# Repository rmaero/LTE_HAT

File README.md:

4G HAT para Raspberry Pi, Diseño completo de un HAT compatible con Raspberry Pi que integra comunicaciones celulares 4G/LTE. Hecho especialmente para usar como companion computer en y comunicarse con un PixHawk en un UAV (unmanned aerial vehicle).
Desarrollado como proyecto final para la materia Diseño Avanzado de Circuitos Impresos en la Universidad Nacional de Rosario.

Dentro del repositorio se van a encontrar 3 versiones del layout apenas diferentes entre si. Estas iteraciones se hicieron en busqueda de optimizar el espacio y la comodidad de los conectores para el usuario (tener en cuenta que una vez estar montado sobre una Raspberry Pi la cara inferior del HAT no es accesible).

Características

Compatible con estándar Raspberry Pi HAT
Cumple especificaciones mecánicas (65x56mm, mounting holes)
EEPROM de identificación según estándar HAT
Conectores GPIO de 40 pines

Comunicacion UART PixHawk:
Conector JST GH 6 pines para conectar con cable cruzado a GPS2 o TELEM2 del PixHawk Cube Orange. 115200 baudios.

Comunicaciones 4G/LTE:

Módulo celular: SIM7600
Bandas soportadas: [especificar]
Interfaz USB para comandos AT
Conectores SMA/U.FL para antenas externas

Diseño RF de Alta Frecuencia

PCB multicapa: 2 capas (esto fue eleccion adrede como ejercicio academico, porque es mas dificil lograr impedancia controlada con esta distancia entre capas).
Control de impedancia de 50Ω en líneas de RF
Control de impedancia de 90Ω en lineas USB 2.0
Stackup optimizado para señales high-speed
Matching de impedancia en conexiones de antena

Alimentación
Pack de baterias 2S a 9S (de 7V a 35V). Regulador switching para alimentar la Raspberry Pi, segundo regulador switching alimenta el modulo SIM7600.

Tecnologías Utilizadas

Diseño PCB: KiCAD 9
Capas: 2 layers (Ground plane en ambas capas)
Comunicación: USB, UART, SPI, GPIO
Impedancia controlada: 50Ω para trazas RF, 90Ω diferencial para USB

Esquematico principal

El esquematico completo puede encontrarse en la carpeta del proyecto.

Estado del Proyecto

-Diseño esquemático completo
-Layout PCB con control de impedancia
-Diseño validado en simulación

Estado actual: Proyecto académico completado (2025). Diseño validado, pendiente fabricación y testing.

Licencia
Proyecto académico - Todos los derechos reservados

Contacto
Rodrigo Maero - r.maero@gmail.com

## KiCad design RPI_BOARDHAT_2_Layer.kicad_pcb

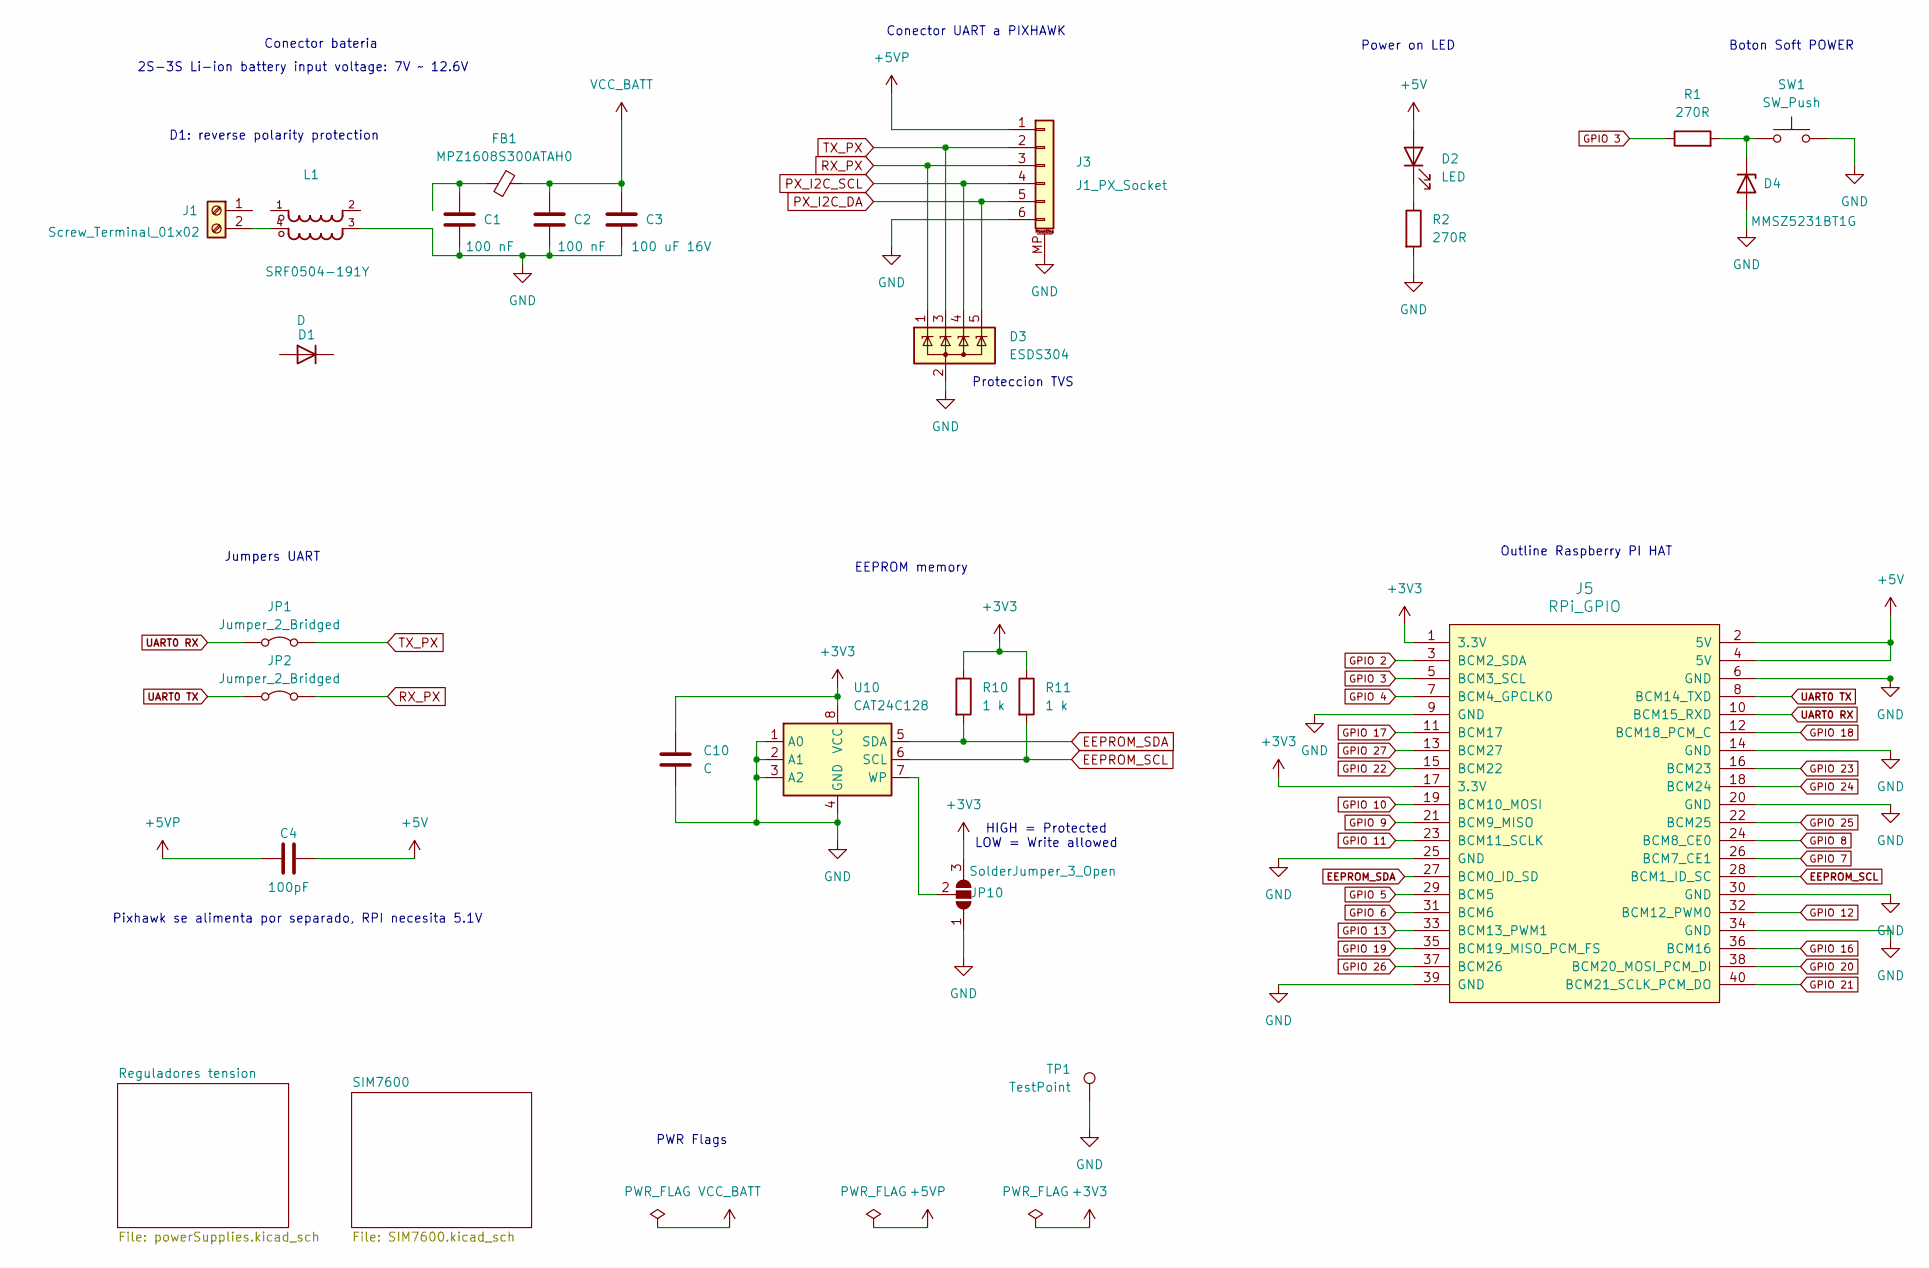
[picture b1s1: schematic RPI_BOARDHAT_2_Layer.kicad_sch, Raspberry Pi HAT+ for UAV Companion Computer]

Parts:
C1, C2: 100 nF; C_0402_1005Metric
C3: 100 uF 16V; C_0402_1005Metric
C4: 100pF; C_0603_1608Metric
C10: C; C_0201_0603Metric
D1: D; D_SMA
D2: LED; LED_0603_1608Metric
D3: ESDS304; SOT-23-5
D4: MMSZ5231BT1G; D_SOD-923
FB1: MPZ1608S300ATAH0; L_0603_1608Metric
J1: Screw_Terminal_01x02; TerminalBlock_bornier-2_P5.08mm
J3: J1_PX_Socket; JST_GH_SM06B-GHS-TB_1x06-1MP_P1.25mm_Horizontal
J5: RPi_GPIO; RPI_Hat_B+
JP1, JP2: Jumper_2_Bridged; SolderJumper-2_P1.3mm_Bridged_RoundedPad1.0x1.5mm
JP10: SolderJumper_3_Open; SolderJumper-3_P1.3mm_Open_Pad1.0x1.5mm_NumberLabels
L1: SRF0504-191Y; FIL_SRF0504-191Y
R1: 270R; R_0201_0603Metric
R2: 270R; R_0603_1608Metric
R10, R11: 1 k; R_0603_1608Metric
SW1: SW_Push; SW_Push_SPST_NO_Alps_SKRK
TP1: TestPoint; TestPoint_2Pads_Pitch2.54mm_Drill0.8mm
U10: CAT24C128; JEITA_SOIC-8_3.9x4.9mm_P1.27mm

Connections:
+3V3: C10.1, J5.1 (3.3V), J5.17 (3.3V), JP10.3 (B), R10.1, R11.1, U10.8 (VCC)
+5V: C4.1, D2.2 (A), J5.2 (5V), J5.4 (5V); also elsewhere on the board
+5VP: C4.2, J3.1
EEPROM_SCL: J5.28 (BCM1_ID_SC), R11.2, U10.6 (SCL)
EEPROM_SDA: J5.27 (BCM0_ID_SD), R10.2, U10.5 (SDA)
GND: C1.2, C2.2, C3.2, C10.2, D3.2 (A), D4.2 (A), J3.6, J3.MP (MountPin), J5.6 (GND), J5.9 (GND), J5.14 (GND), J5.20 (GND), J5.25 (GND), J5.30 (GND), J5.34 (GND), J5.39 (GND), JP10.1 (A), L1.3, R2.2, SW1.2, TP1.1, U10.1 (A0), U10.2 (A1), U10.3 (A2), U10.4 (GND); also elsewhere on the board
GPIO 2: J5.3 (BCM2_SDA)
GPIO 3: J5.5 (BCM3_SCL), R1.1
GPIO 4: J5.7 (BCM4_GPCLK0)
GPIO 5: J5.29 (BCM5)
GPIO 6: J5.31 (BCM6)
GPIO 7: J5.26 (BCM7_CE1)
GPIO 8: J5.24 (BCM8_CE0)
GPIO 9: J5.21 (BCM9_MISO)
GPIO 10: J5.19 (BCM10_MOSI)
GPIO 11: J5.23 (BCM11_SCLK)
GPIO 12: J5.32 (BCM12_PWM0)
GPIO 13: J5.33 (BCM13_PWM1)
GPIO 16: J5.36 (BCM16)
GPIO 17: J5.11 (BCM17)
GPIO 18: J5.12 (BCM18_PCM_C)
GPIO 19: J5.35 (BCM19_MISO_PCM_FS)
GPIO 20: J5.38 (BCM20_MOSI_PCM_DI)
GPIO 21: J5.40 (BCM21_SCLK_PCM_DO)
GPIO 22: J5.15 (BCM22)
GPIO 23: J5.16 (BCM23)
GPIO 24: J5.18 (BCM24)
GPIO 25: J5.22 (BCM25)
GPIO 26: J5.37 (BCM26)
GPIO 27: J5.13 (BCM27)
unnamed: D1.2 (A), L1.2
unnamed: D2.1 (K), R2.1
unnamed: D4.1 (K), R1.2, SW1.1
unnamed: J1.1, L1.1
unnamed: J1.2, L1.4
unnamed: JP10.2 (C), U10.7 (WP)
PX_I2C_DA: D3.5 (K), J3.5
PX_I2C_SCL: D3.4 (K), J3.4
RX_PX: D3.1 (K), J3.3, JP2.2 (B)
TX_PX: D3.3 (K), J3.2, JP1.2 (B)
UART0 RX: J5.10 (BCM15_RXD), JP1.1 (A)
UART0 TX: J5.8 (BCM14_TXD), JP2.1 (A)
VCC_BATT: C2.1, C3.1, FB1.2; also elsewhere on the board

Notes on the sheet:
2S-3S Li-ion battery input voltage: 7V ~ 12.6V
Proteccion TVS
PWR Flags
Pixhawk se alimenta por separado, RPI necesita 5.1V
D1: reverse polarity protection
EEPROM memory
Outline Raspberry PI HAT
Conector UART a PIXHAWK
Jumpers UART
HIGH = Protected LOW = Write allowed
Boton Soft POWER
Conector bateria
Power on LED

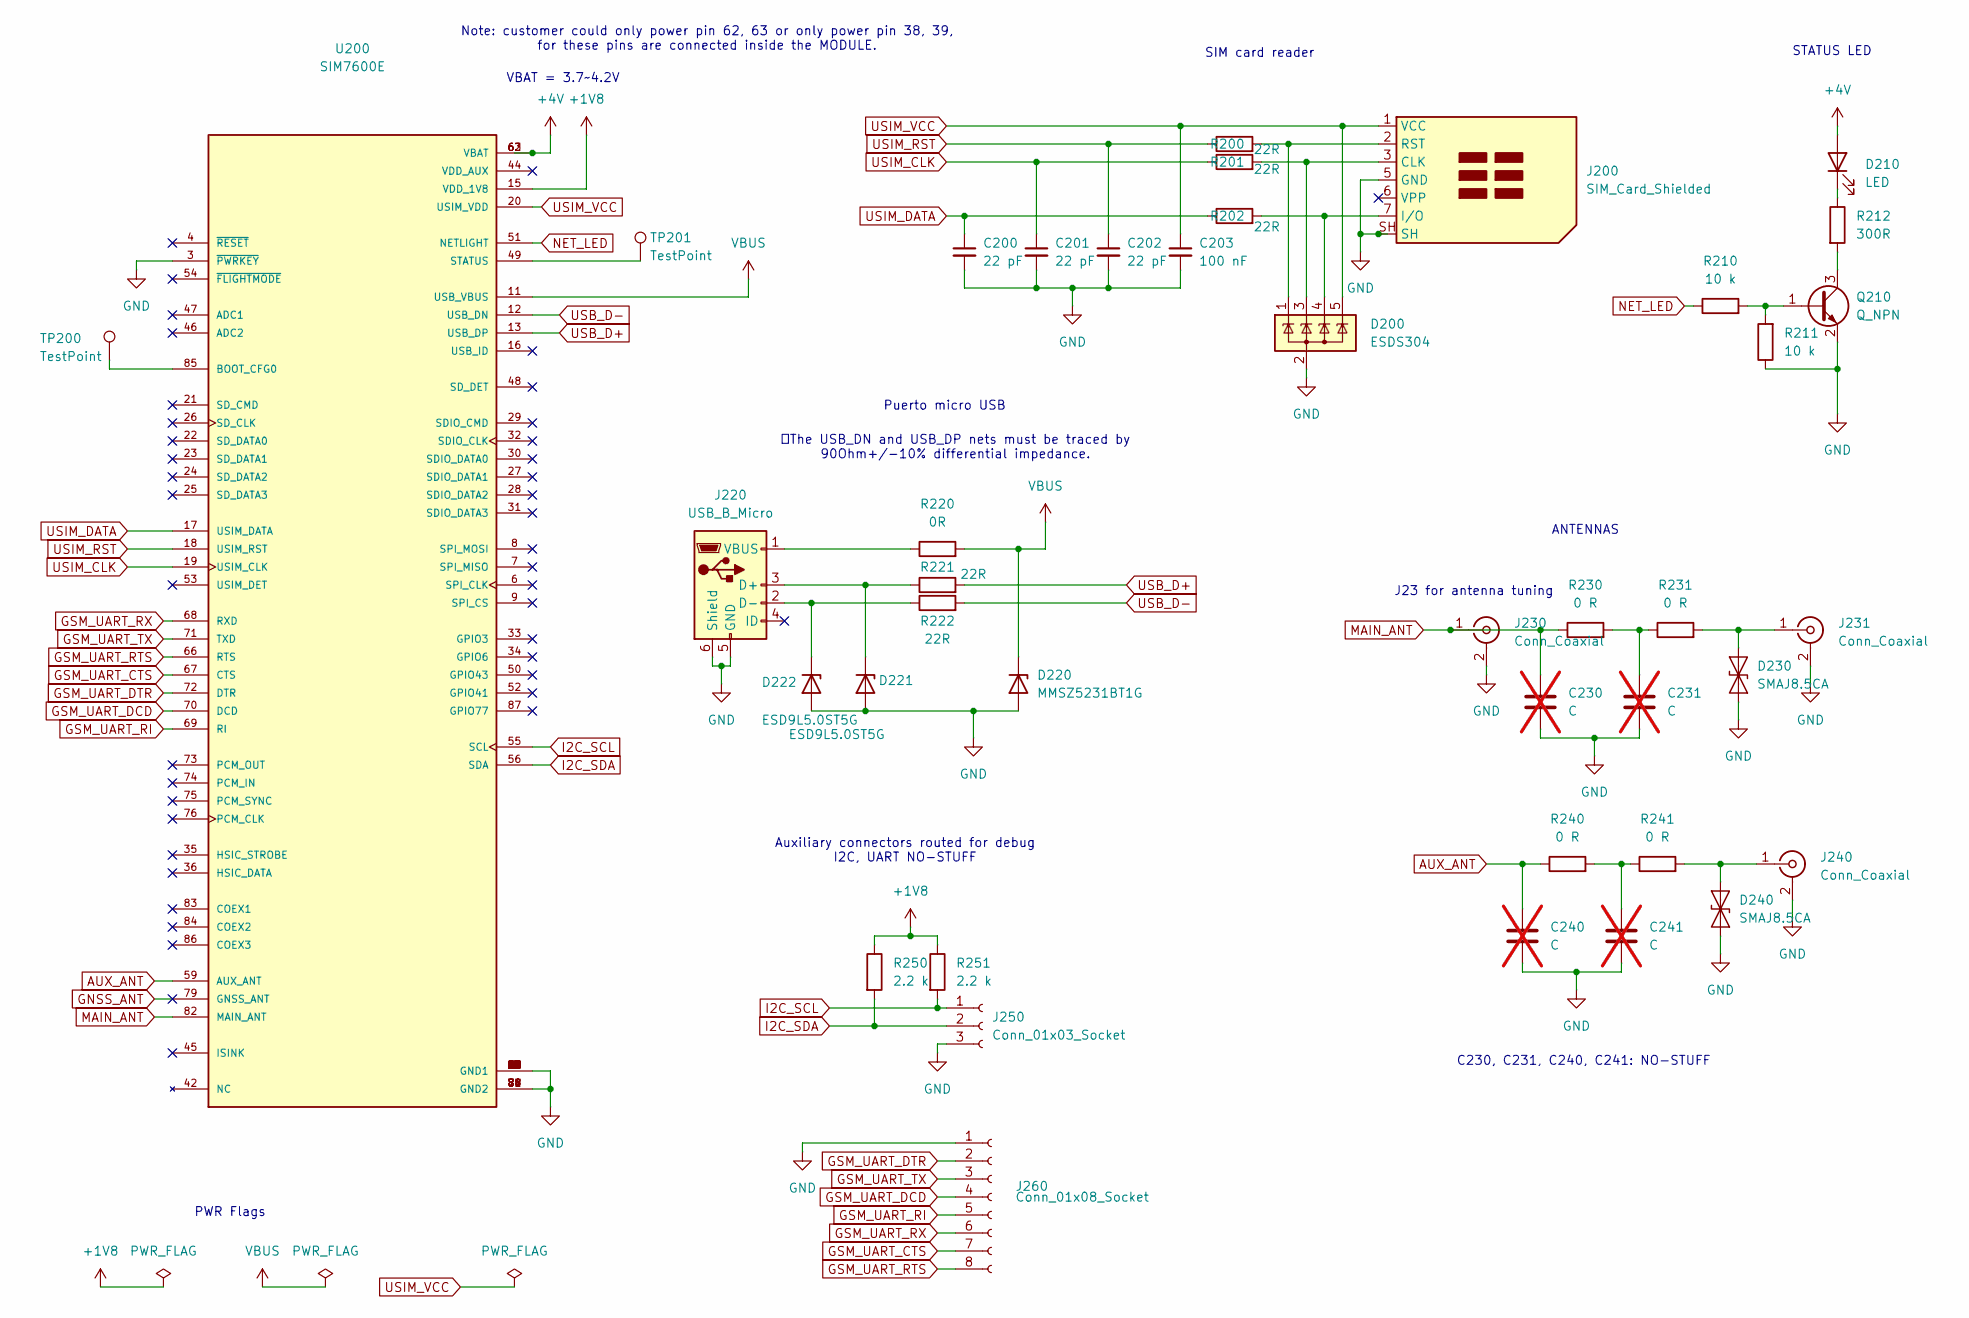
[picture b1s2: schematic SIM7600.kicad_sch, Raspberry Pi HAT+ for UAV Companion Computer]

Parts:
C200, C201, C202: 22 pF; C_0201_0603Metric
C203: 100 nF; C_0201_0603Metric
C230, C231, C240, C241: C; C_0402_1005Metric_Pad0.74x0.62mm_HandSolder; not fitted
D200: ESDS304; SOT-23-5
D210: LED; LED_0603_1608Metric
D220: MMSZ5231BT1G; D_SOD-123
D221, D222: ESD9L5.0ST5G; D_SOD-923
D230, D240: SMAJ8.5CA; D_0402_1005Metric
J200: SIM_Card_Shielded; nanoSIM_GCT_SIM8060-6-0-14-00
J220: USB_B_Micro; USB_Micro-B_Molex-105017-0001
J230, J231, J240: Conn_Coaxial; U.FL_Hirose_U.FL-R-SMT-1_Vertical
J250: Conn_01x03_Socket; JST_SH_BM03B-SRSS-TB_1x03-1MP_P1.00mm_Vertical
J260: Conn_01x08_Socket; JST_SH_BM08B-SRSS-TB_1x08-1MP_P1.00mm_Vertical
Q210: Q_NPN; SOT-23
R200, R201, R202: 22R; R_0201_0603Metric
R210, R211: 10 k; R_0201_0603Metric
R212: 300R; R_0201_0603Metric
R220: 0R; R_0201_0603Metric
R221, R222: 22R; R_0603_1608Metric
R230, R231, R240, R241: 0 R; R_0603_1608Metric_Pad0.98x0.95mm_HandSolder
R250, R251: 2.2 k; R_0201_0603Metric
TP200, TP201: TestPoint; TestPoint_Pad_D1.0mm
U200: SIM7600E; XCVR_SIM7600E; PARTREV V1.03

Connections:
+1V8: R250.1, R251.1, U200.15 (VDD_1V8)
+4V: D210.2 (A), U200.62 (VBAT), U200.63 (VBAT); also elsewhere on the board
AUX_ANT: C240.1, R240.1, U200.59 (AUX_ANT)
GND: C200.2, C201.2, C202.2, C203.2, C230.2, C231.2, C240.2, C241.2, D200.2 (A), D220.2 (A), D221.2 (A), D222.2 (A), D230.1 (A1), D240.1 (A1), J200.5 (GND), J200.SH, J220.5 (GND), J220.6 (Shield), J230.2 (Ext), J231.2 (Ext), J240.2 (Ext), J250.3, J260.1, Q210.2 (E), R211.1, U200.1 (GND1), U200.2 (GND1), U200.3 (~PWRKEY), U200.5 (GND1), U200.10 (GND1), U200.14 (GND1), U200.37 (GND1), U200.40 (GND1), U200.41 (GND1), U200.43 (GND1), U200.57 (GND1), U200.58 (GND1), U200.60 (GND1), U200.61 (GND1), U200.64 (GND1), U200.65 (GND1), U200.77 (GND2), U200.78 (GND2), U200.80 (GND2), U200.81 (GND2); also elsewhere on the board
GNSS_ANT: U200.79 (GNSS_ANT)
GSM_UART_CTS: J260.7, U200.67 (CTS)
GSM_UART_DCD: J260.4, U200.70 (DCD)
GSM_UART_DTR: J260.2, U200.72 (DTR)
GSM_UART_RI: J260.5, U200.69 (RI)
GSM_UART_RTS: J260.8, U200.66 (RTS)
GSM_UART_RX: J260.6, U200.68 (RXD)
GSM_UART_TX: J260.3, U200.71 (TXD)
I2C_SCL: J250.1, R251.2, U200.55 (SCL)
I2C_SDA: J250.2, R250.2, U200.56 (SDA)
MAIN_ANT: C230.1, J230.1 (In), R230.1, U200.82 (MAIN_ANT)
NET_LED: R210.1, U200.51 (NETLIGHT)
unnamed: C231.1, R230.2, R231.1
unnamed: C241.1, R240.2, R241.1
unnamed: D210.1 (K), R212.1
unnamed: D221.1 (K), J220.3 (D+), R221.1
unnamed: D222.1 (K), J220.2 (D-), R222.1
unnamed: D230.2 (A2), J231.1 (In), R231.2
unnamed: D240.2 (A2), J240.1 (In), R241.2
unnamed: D200.3 (K), J200.3 (CLK), R201.2
unnamed: D200.4 (K), J200.7 (I/O), R202.2
unnamed: D200.1 (K), J200.2 (RST), R200.2
unnamed: J220.1 (VBUS), R220.1
unnamed: Q210.1 (B), R210.2, R211.2
unnamed: Q210.3 (C), R212.2
unnamed: TP200.1, U200.85 (BOOT_CFG0)
unnamed: TP201.1, U200.49 (STATUS)
USB_D+: R221.2, U200.13 (USB_DP)
USB_D-: R222.2, U200.12 (USB_DN)
USIM_CLK: C201.1, R201.1, U200.19 (USIM_CLK)
USIM_DATA: C200.1, R202.1, U200.17 (USIM_DATA)
USIM_RST: C202.1, R200.1, U200.18 (USIM_RST)
USIM_VCC: C203.1, D200.5 (K), J200.1 (VCC), U200.20 (USIM_VDD)
VBUS: D220.1 (K), R220.2, U200.11 (USB_VBUS)

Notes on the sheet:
SIM card reader
Auxiliary connectors routed for debug I2C, UART NO-STUFF
STATUS LED
Puerto micro USB
VBAT = 3.7~4.2V
PWR Flags
C230, C231, C240, C241: NO-STUFF
Note: customer could only power pin 62, 63 or only power pin 38, 39, for these pins are connected inside the MODULE.
ANTENNAS
J23 for antenna tuning
：The USB_DN and USB_DP nets must be traced by 90Ohm+/-10% differential impedance.

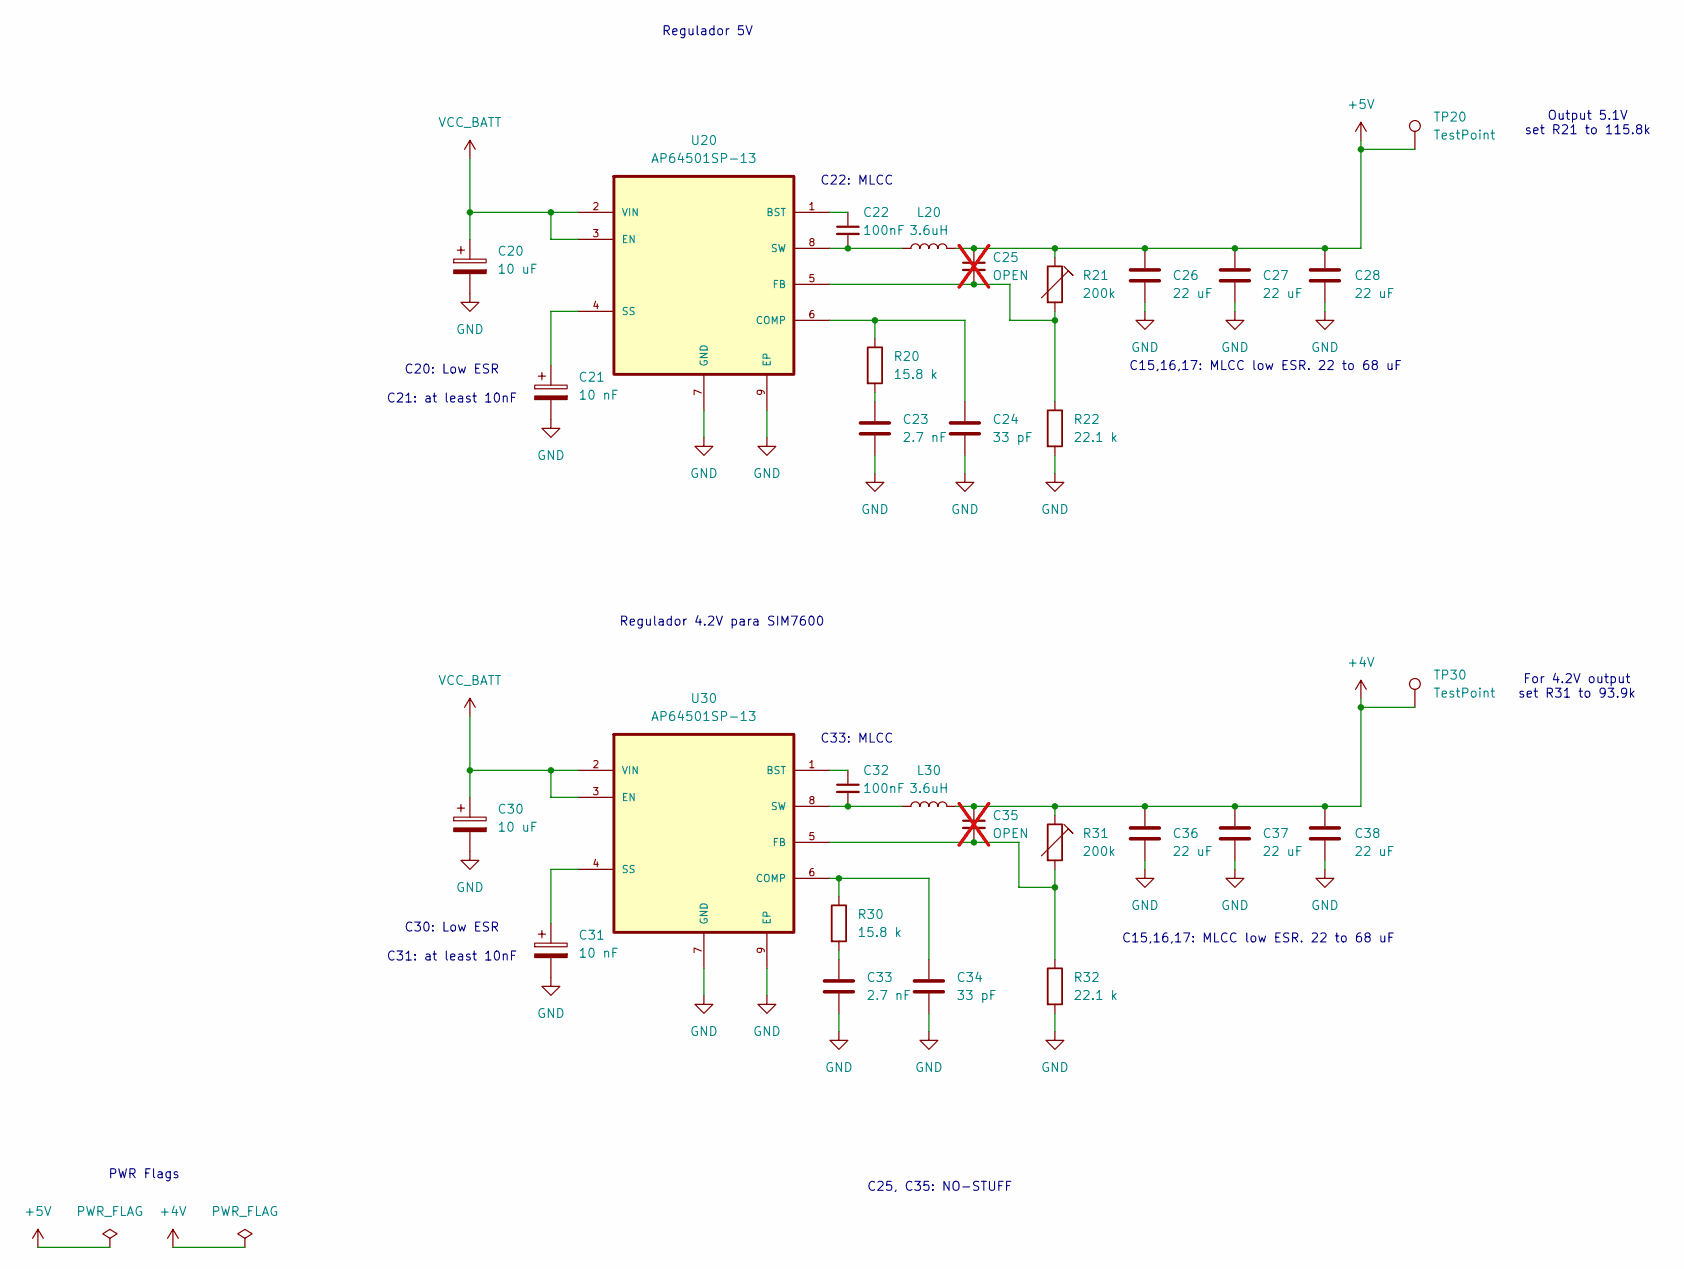
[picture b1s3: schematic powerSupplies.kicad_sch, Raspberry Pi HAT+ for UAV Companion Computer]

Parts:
C20, C30: 10 uF; C_0603_1608Metric
C21, C31: 10 nF; C_0603_1608Metric
C22, C32: 100nF; C_0603_1608Metric
C23, C33: 2.7 nF; C_0603_1608Metric
C24, C34: 33 pF; C_0603_1608Metric
C25, C35: OPEN; C_0201_0603Metric; not fitted
C26, C27, C28, C36, C37, C38: 22 uF; C_0603_1608Metric
L20, L30: 3.6uH; L_12x12mm_H8mm
R20, R30: 15.8 k; R_0603_1608Metric
R21, R31: 200k; Potentiometer_Bourns_3214X_Vertical
R22, R32: 22.1 k; R_0603_1608Metric
TP20, TP30: TestPoint; TestPoint_Pad_D1.0mm
U20, U30: AP64501SP-13; SOIC127P600X170-9N

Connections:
+4V: C35.1, C36.1, C37.1, C38.1, L30.2, R31.1, TP30.1; also elsewhere on the board
+5V: C25.1, C26.1, C27.1, C28.1, L20.2, R21.1, TP20.1; also elsewhere on the board
GND: C20.2, C21.2, C23.2, C24.2, C26.2, C27.2, C28.2, C30.2, C31.2, C33.2, C34.2, C36.2, C37.2, C38.2, R22.2, R32.2, U20.7 (GND), U20.9 (EP), U30.7 (GND), U30.9 (EP); also elsewhere on the board
unnamed: C23.1, R20.2
unnamed: C33.1, R30.2
unnamed: C22.1, U20.1 (BST)
unnamed: C24.1, R20.1, U20.6 (COMP)
unnamed: C25.2, R21.2, R22.1, U20.5 (FB)
unnamed: C21.1, U20.4 (SS)
unnamed: C22.2, L20.1, U20.8 (SW)
unnamed: C32.1, U30.1 (BST)
unnamed: C34.1, R30.1, U30.6 (COMP)
unnamed: C35.2, R31.2, R32.1, U30.5 (FB)
unnamed: C31.1, U30.4 (SS)
unnamed: C32.2, L30.1, U30.8 (SW)
VCC_BATT: C20.1, C30.1, U20.2 (VIN), U20.3 (EN), U30.2 (VIN), U30.3 (EN); also elsewhere on the board

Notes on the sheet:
C30: Low ESR C31: at least 10nF
Regulador 4.2V para SIM7600
Regulador 5V
C20: Low ESR C21: at least 10nF
C25, C35: NO-STUFF
C15,16,17: MLCC low ESR. 22 to 68 uF
For 4.2V output set R31 to 93.9k
C33: MLCC
C22: MLCC
Output 5.1V set R21 to 115.8k
PWR Flags

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
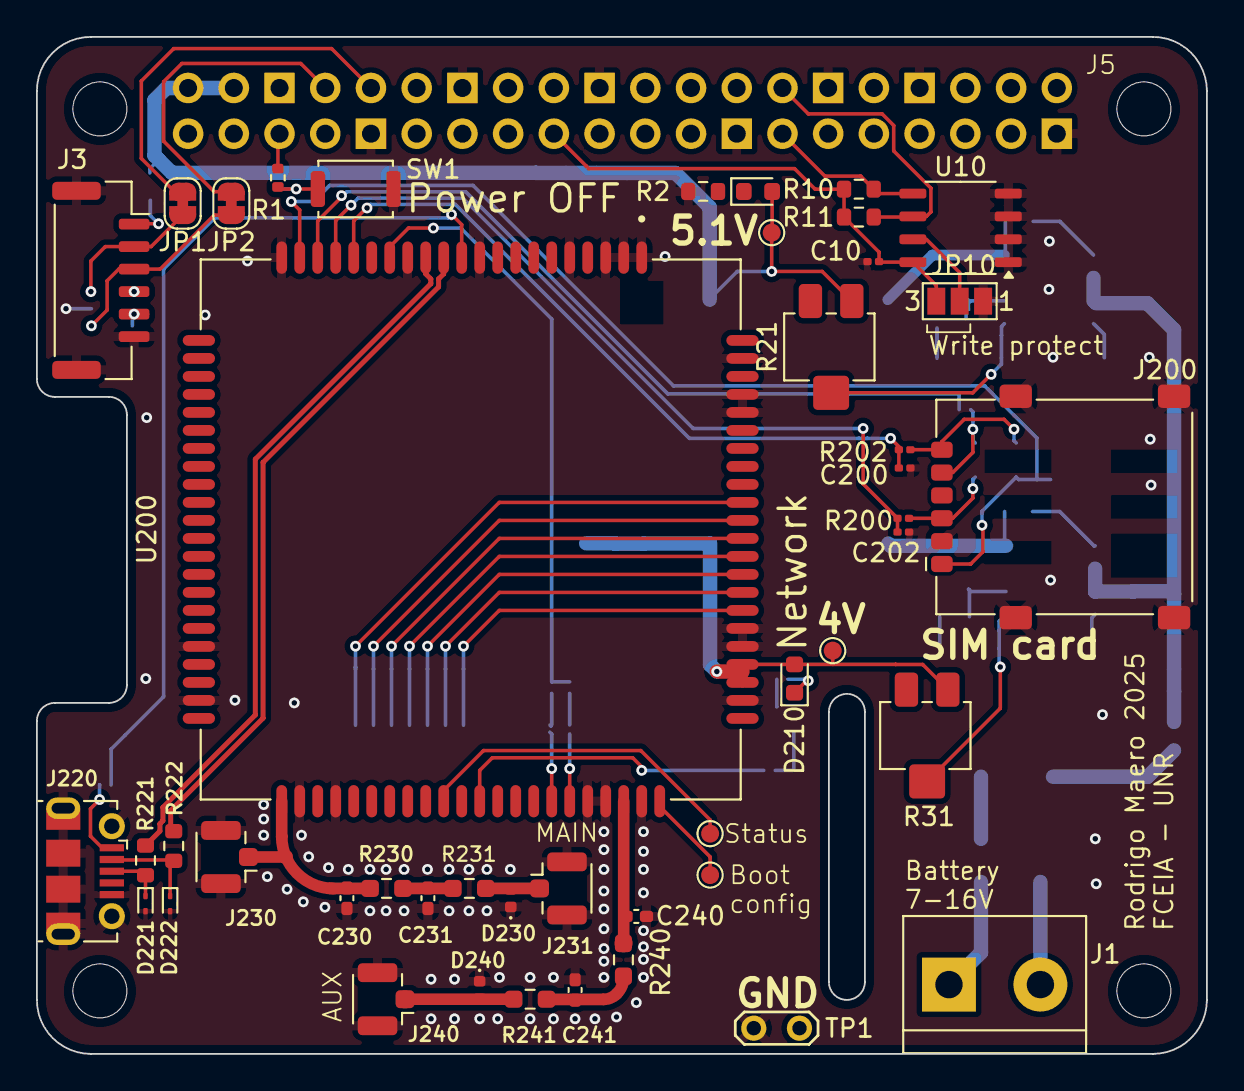
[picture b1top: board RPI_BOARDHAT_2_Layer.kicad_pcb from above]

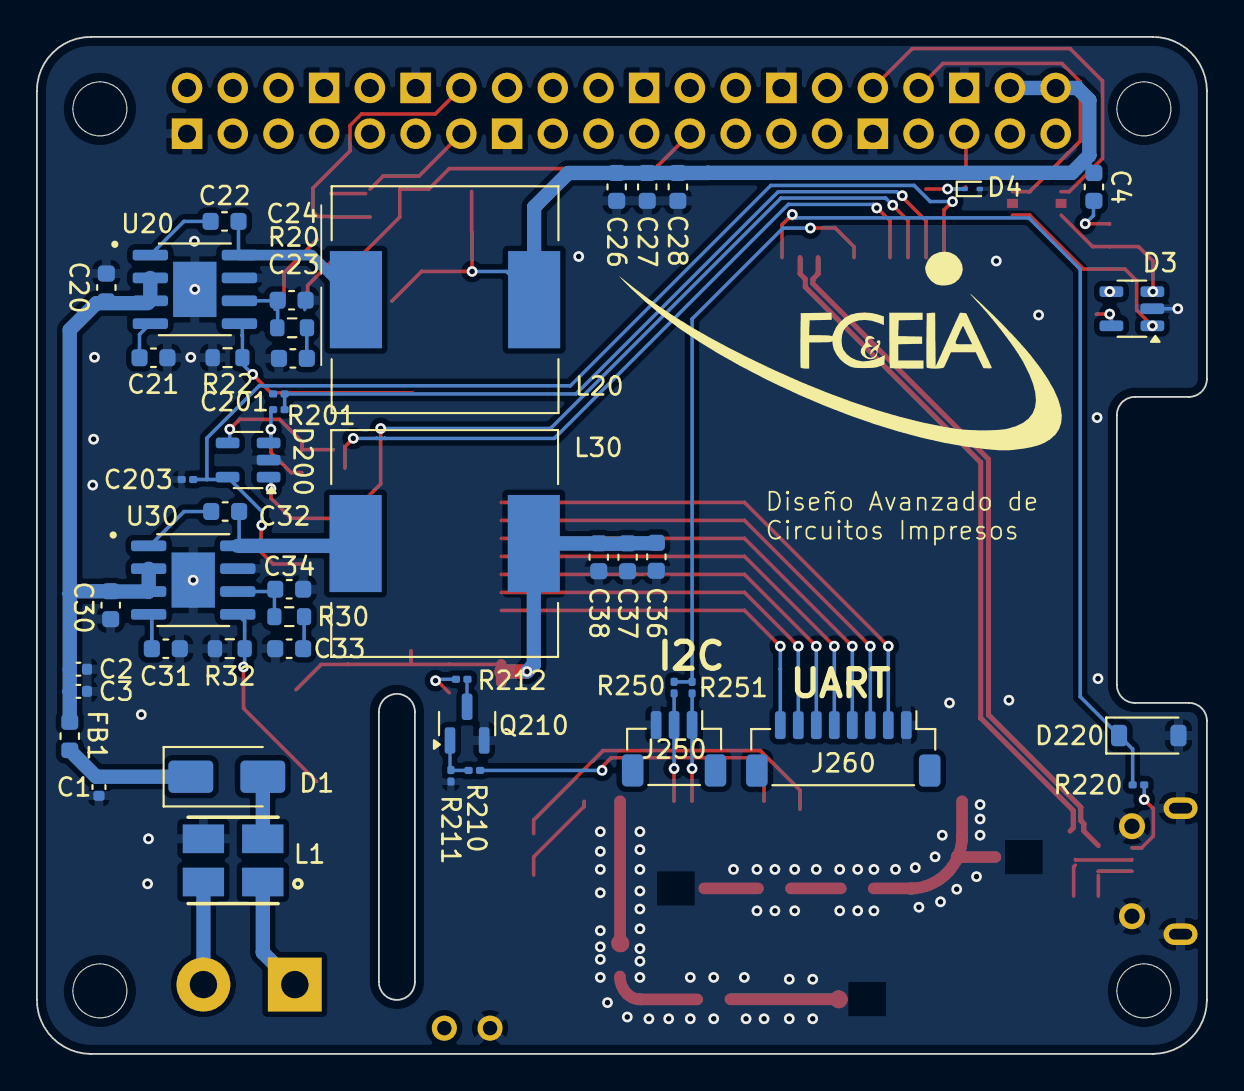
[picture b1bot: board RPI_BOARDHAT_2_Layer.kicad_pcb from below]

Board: 2 copper layers, 65.0 x 56.5 mm, 93 parts (47 on the bottom side), 69 nets.

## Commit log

2026-01-02 Disenio final para materia electiva
